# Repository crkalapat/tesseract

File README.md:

# Tesseract

_An open-source smart speaker for your AI agent_

<p align="center">
  
  <br>
  <br>
  <a href="https://www.youtube.com/watch?v=WYpaCrV-wes">▶ Watch the demo (2:15)</a>
</p>
<br>

## Status

- [x] Enclosure CAD and PCB design
- [x] v1 boards fabricated
- [x] Assembly
- [x] Firmware
- [x] Hermes agent integration
- [ ] Dynamic feature generation
- [ ] Smart home integration

## Next Steps

- Personalized software: Tesseract is able to add new features to its code just by you describing them with your voice. For example, a stock ticker widget on the clock screen.

- Smart home integration: Tesseract acts as an endpoint that can connect control to your AI app of choice to let you control your home's devices

## Hardware

### Features

- Crisp 1.91" Square OLED Display
- 9 RGB WS2812b LEDs (on a strip)
- Compact 4 Ohm Speaker
- 4 Programmable Buttons
- Built-in Microphone
- 2.4 GHz Wi-Fi
- Powered via USB-C

Tesseract runs on a Raspberry Pi Zero 2W connected to a custom PCB that links it to a microphone, speaker, display, buttons, and an LED strip. The hardware mainly does cloud API calls, but still runs a wake-word detection model locally.

Tesseract also works as an alarm clock. The main reason I went with an OLED display was so there could be a true black (not like that on an LCD) at night.

The alarm clock is also where the name "Tesseract" came from, since the project is literally a cube with time (a clock face) inside it, kind of like a 4D cube.

## Firmware

### Features

- Hermes Agent compatibility
- Spotify compatibility
- Quiet mode, so finished agent tasks wait for you instead of interrupting
- Night mode to dim screen
- Timers, alarms, weather, and more

Say "Franklin" and ask anything. The firmware in [`code/`](code/README.md) handles on-device wake word
detection, streams speech-to-text, the LLM and text-to-speech through OpenRouter, drives the clock
display (with captions while it talks) and LED strip, and runs timers and alarms.

Simple commands (timers, volume, music controls) are handled on the device. Questions go to a fast model
(currently `gpt-oss-120b`), and anything involving your own stuff (calendar, email, documents) or several
steps goes to your own AI agent (Hermes Agent is currently supported). More details about the code,
setup, pinout and bring-up steps are in [code/README.md](code/README.md).

## Schematic

## PCB

## Wiring Diagram

## CAD

You can find the STEP file for the assembled version of Tesseract in the `cad/` directory along with printable
STL files. If you prefer, you can also [view the project in OnShape.](https://cad.onshape.com/documents/c663113203f550a8dc1a02a8/w/2121a6af79302a6b1759fafd/e/e3a5e453c89e8346d1915b92)
Or alternatively, you can find renders of the CAD in the `assets/` subdirectory.

## BOM

_More detailed BOM with links can be found under BOM.csv in main directory_

| Name                               | Quantity | Total Price |
| ---------------------------------- | -------: | ----------: |
| 6mm Buttons                        |        4 |       $1.48 |
| JST XH Cable Connector Kit         |        1 |      $15.79 |
| Raspberry Pi Zero 2W               |        1 |      $19.05 |
| NHD 1.91" OLED Display             |        1 |      $35.70 |
| 0.1uF Capacitors                   |        5 |       $0.95 |
| 10uF Capacitors                    |        5 |       $1.15 |
| 100k Resistors                     |        3 |       $0.90 |
| 210k Resistors                     |        3 |       $0.72 |
| 4Ohm 3W Speaker                    |        1 |      $11.57 |
| PCB                                |        1 |       $3.20 |
| PCB Stencil                        |        1 |       $7.16 |
| MAX98357AETE+T Speaker IC          |        1 |       $3.73 |
| DMM-4026-B-I2S-R Microphone        |        1 |       $2.94 |
| USB-C Breakout Board               |        1 |       $1.62 |
| (Owned) M2.5×8 Screws              |        4 |       $0.00 |
| (Owned) M3×8 Screws                |       12 |       $0.00 |
| (Owned) M3×12 Screws               |        4 |       $0.00 |
| (Owned) M3 Nuts                    |       16 |       $0.00 |
| (Owned) M2.5 Nuts                  |        4 |       $0.00 |
| 2" Plastic 2477 Square             |        1 |       $1.00 |
| (3D Printed) Case                  |        1 |       $0.00 |
| (3D Printed) Display Cover         |        1 |       $0.00 |
| (3D Printed) Speaker Assembly Case |        1 |       $0.00 |
| (3D Printed) Speaker Assembly Lid  |        1 |       $0.00 |
| (3D Printed) LED Chamber           |        1 |       $0.00 |
| (3D Printed) Button Caps           |        4 |       $0.00 |
| M3 Heat-Set Threaded Insert Bag    |        1 |       $3.56 |
| WS2812b LED Strip                  |        1 |       $6.22 |
| Rubber Feet Pack                   |        1 |       $1.93 |
| AliExpress Discounts               |          |      -$8.38 |

### Other Expenses

| Item                      |        Cost |
| ------------------------- | ----------: |
| Tariffs                   |       $8.79 |
| Mouser Tax                |       $5.78 |
| Adafruit Tax              |       $1.60 |
| AliExpress Tax            |       $1.30 |
| JLCPCB Shipping           |      $23.58 |
| T&T Plastic Land Shipping |       $8.00 |
| Mouser Shipping           |       $8.49 |
| Adafruit Shipping         |       $6.37 |
| **Total**                 | **$174.20** |

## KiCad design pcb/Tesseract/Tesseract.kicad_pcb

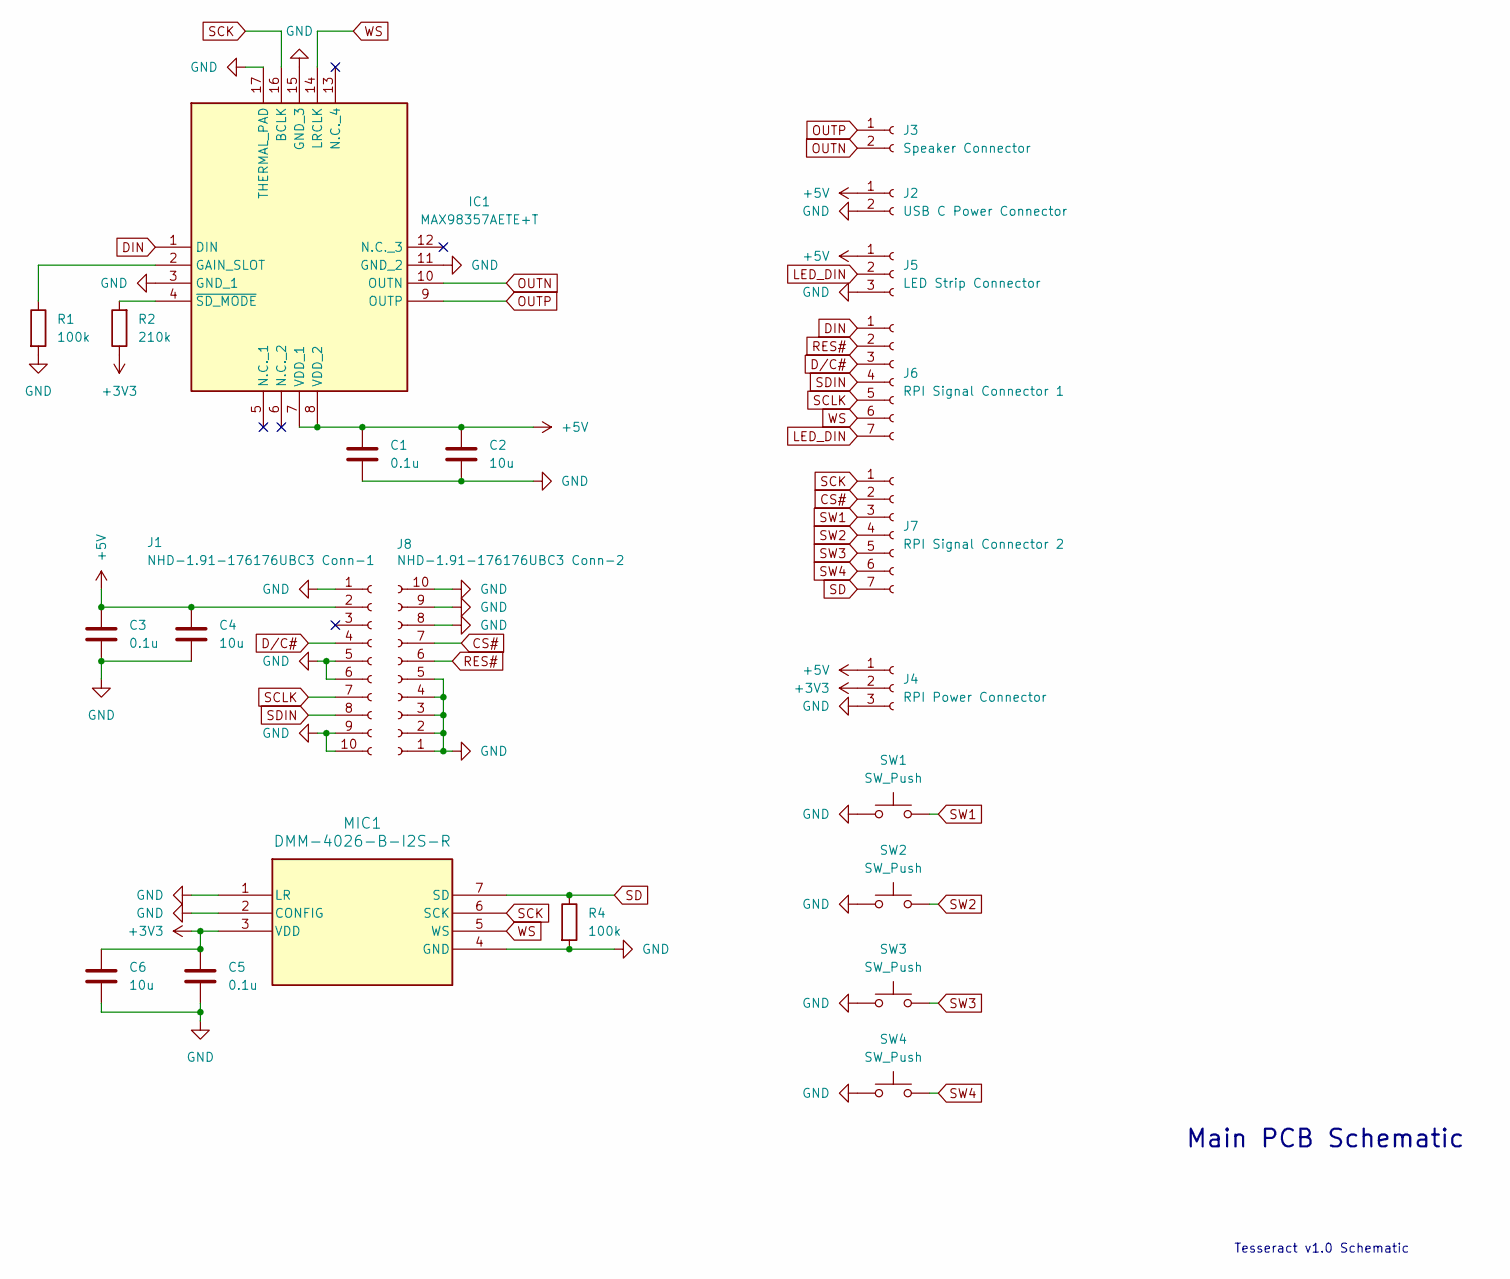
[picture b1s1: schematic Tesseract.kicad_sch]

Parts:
C1, C3, C5: 0.1u; C_0805_2012Metric_Pad1.18x1.45mm_HandSolder
C2, C4, C6: 10u; C_0805_2012Metric_Pad1.18x1.45mm_HandSolder
IC1: MAX98357AETE+T; QFN50P300X300X80-17N; Mouser Part Number 700-MAX98357AETE+T
J1: NHD-1.91-176176UBC3 Conn-1; JST_XH_B10B-XH-A_1x10_P2.50mm_Vertical
J2: USB C Power Connector; JST_XH_B2B-XH-A_1x02_P2.50mm_Vertical
J3: Speaker Connector; JST_XH_B2B-XH-A_1x02_P2.50mm_Vertical
J4: RPI Power Connector; JST_XH_B3B-XH-A_1x03_P2.50mm_Vertical
J5: LED Strip Connector; JST_XH_B3B-XH-A_1x03_P2.50mm_Vertical
J6: RPI Signal Connector 1; JST_XH_B7B-XH-A_1x07_P2.50mm_Vertical
J7: RPI Signal Connector 2; JST_XH_B7B-XH-A_1x07_P2.50mm_Vertical
J8: NHD-1.91-176176UBC3 Conn-2; JST_XH_B10B-XH-A_1x10_P2.50mm_Vertical
MIC1: DMM-4026-B-I2S-R; MIC_DMM-4026-B-I2S-R_PUI
R1, R4: 100k; R_0805_2012Metric_Pad1.20x1.40mm_HandSolder
R2: 210k; R_0805_2012Metric_Pad1.20x1.40mm_HandSolder
SW1, SW2, SW3, SW4: SW_Push; SW_PUSH_6mm_H9.5mm

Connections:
+3V3: C5.1, C6.1, J4.2, MIC1.3 (VDD), R2.1
+5V: C1.1, C2.1, C3.2, C4.1, IC1.7 (VDD_1), IC1.8 (VDD_2), J1.2, J2.1, J4.1, J5.1
CS#: J7.2, J8.7
DIN: IC1.1 (DIN), J6.1
D/C#: J1.4, J6.3
GND: C1.2, C2.2, C3.1, C4.2, C5.2, C6.2, IC1.3 (GND_1), IC1.11 (GND_2), IC1.15 (GND_3), IC1.17 (THERMAL_PAD), J1.1, J1.5, J1.6, J1.9, J1.10, J2.2, J4.3, J5.3, J8.1, J8.2, J8.3, J8.4, J8.5, J8.8, J8.9, J8.10, MIC1.1 (LR), MIC1.2 (CONFIG), MIC1.4 (GND), R1.2, R4.2, SW1.1, SW2.1, SW3.1, SW4.1
LED_DIN: J5.2, J6.7
unnamed: IC1.2 (GAIN_SLOT), R1.1
unnamed: IC1.4 (~SD_MODE), R2.2
OUTN: IC1.10 (OUTN), J3.2
OUTP: IC1.9 (OUTP), J3.1
RES#: J6.2, J8.6
SCK: IC1.16 (BCLK), J7.1, MIC1.6 (SCK)
SCLK: J1.7, J6.5
SD: J7.7, MIC1.7 (SD), R4.1
SDIN: J1.8, J6.4
SW1: J7.3, SW1.2
SW2: J7.4, SW2.2
SW3: J7.5, SW3.2
SW4: J7.6, SW4.2
WS: IC1.14 (LRCLK), J6.6, MIC1.5 (WS)

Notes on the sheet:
Main PCB Schematic
Tesseract v1.0 Schematic

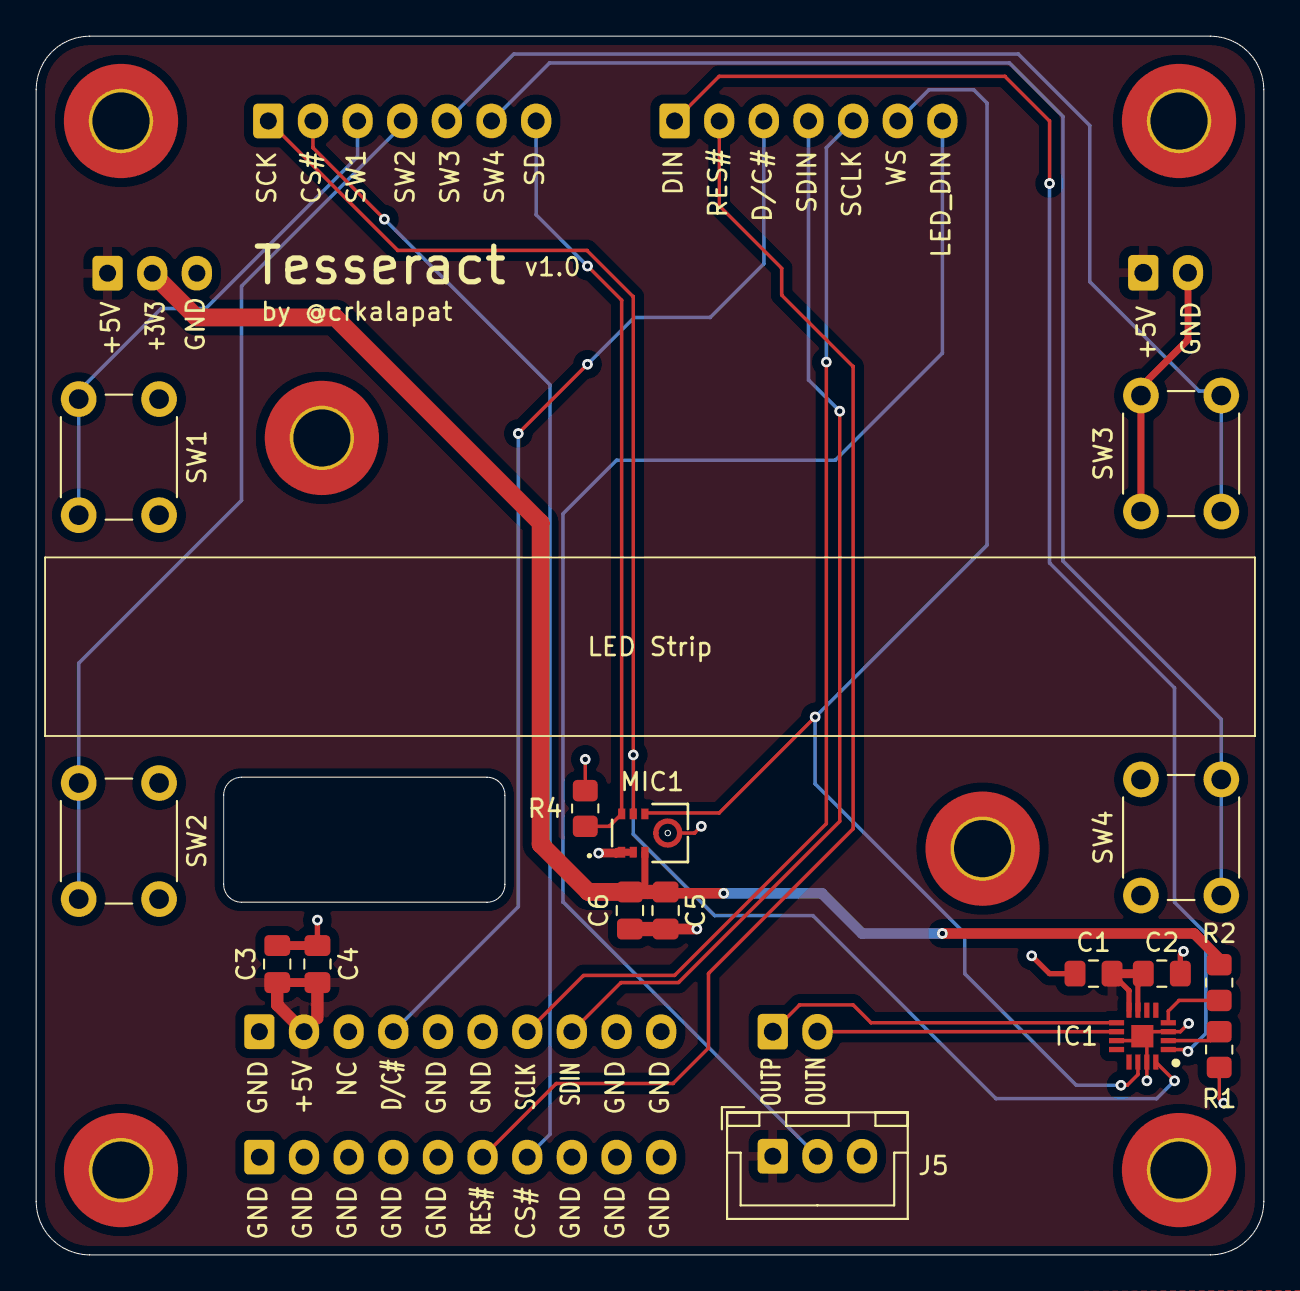
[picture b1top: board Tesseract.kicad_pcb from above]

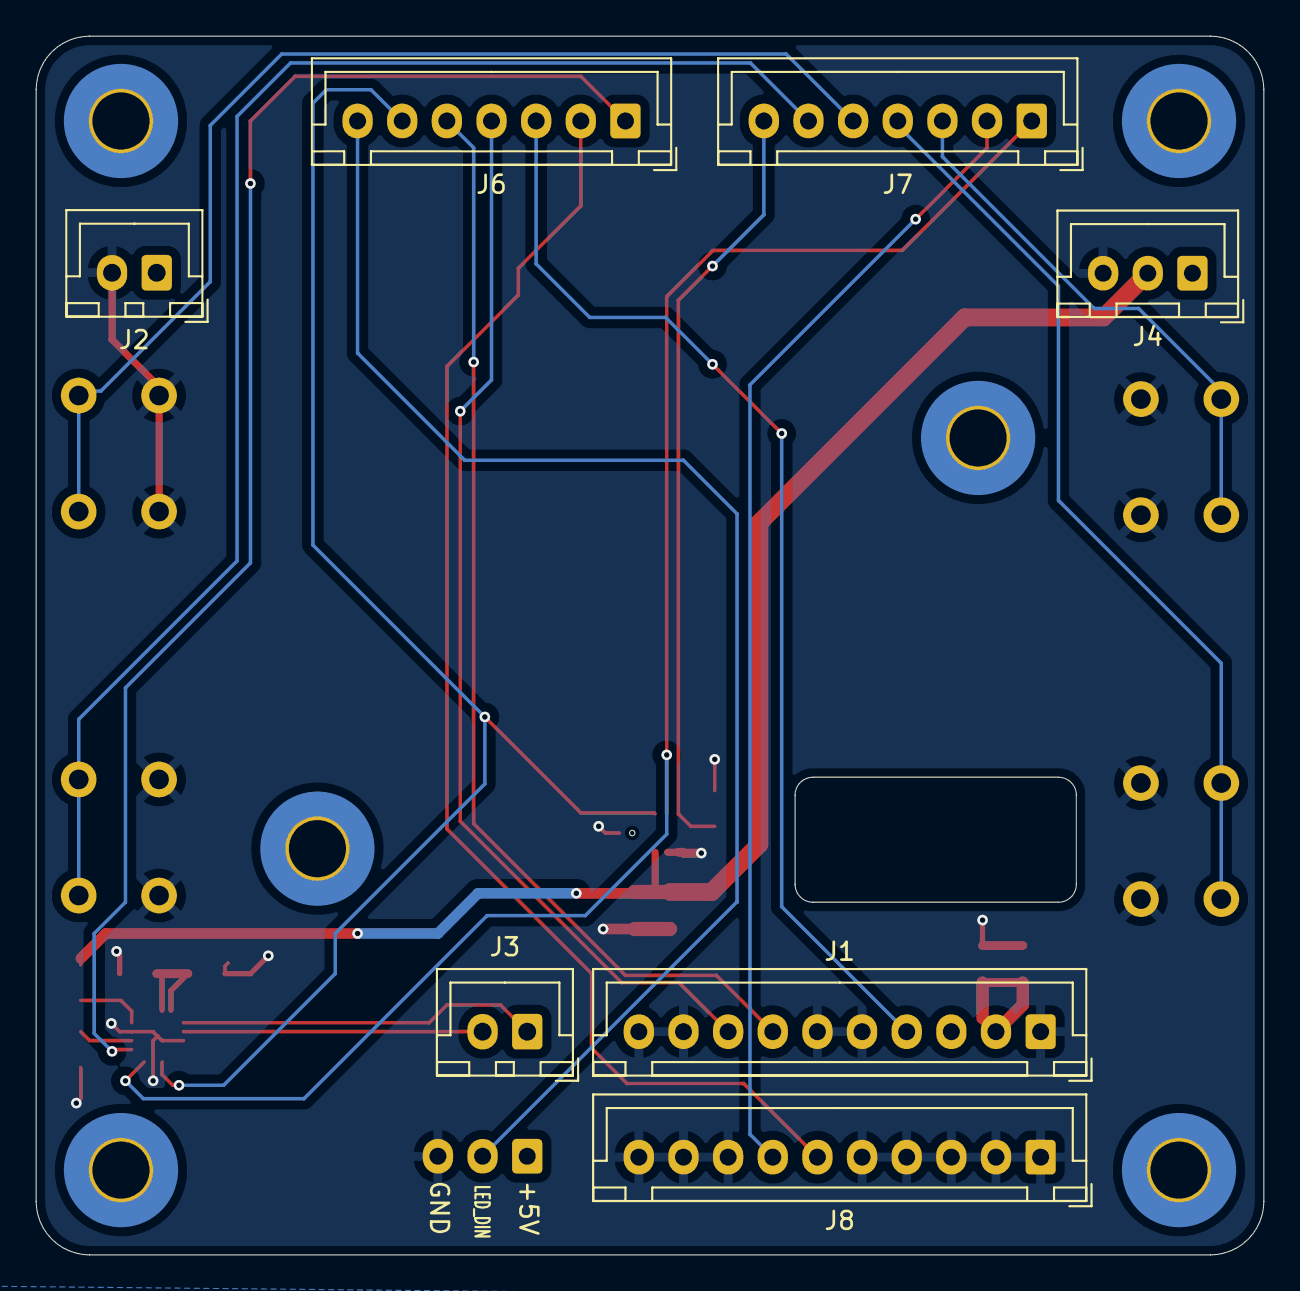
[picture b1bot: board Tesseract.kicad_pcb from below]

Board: 2 copper layers, 68.8 x 68.2 mm, 23 parts (7 on the bottom side), 21 nets.

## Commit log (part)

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2026-06-18 Intial commit
2026-06-30 Add yesterday's work into journal
2026-06-30 Add gitignore and journal picture
2026-06-30 Add early version of PCB files
2026-06-30 Retroactively add devlogs to journal
